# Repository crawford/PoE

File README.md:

# Power over Ethernet #

## Development ###

This project makes use of git commit hooks. Configure git to use them by running the following from the root of the repository:

    git config --local core.hooksPath .githooks/

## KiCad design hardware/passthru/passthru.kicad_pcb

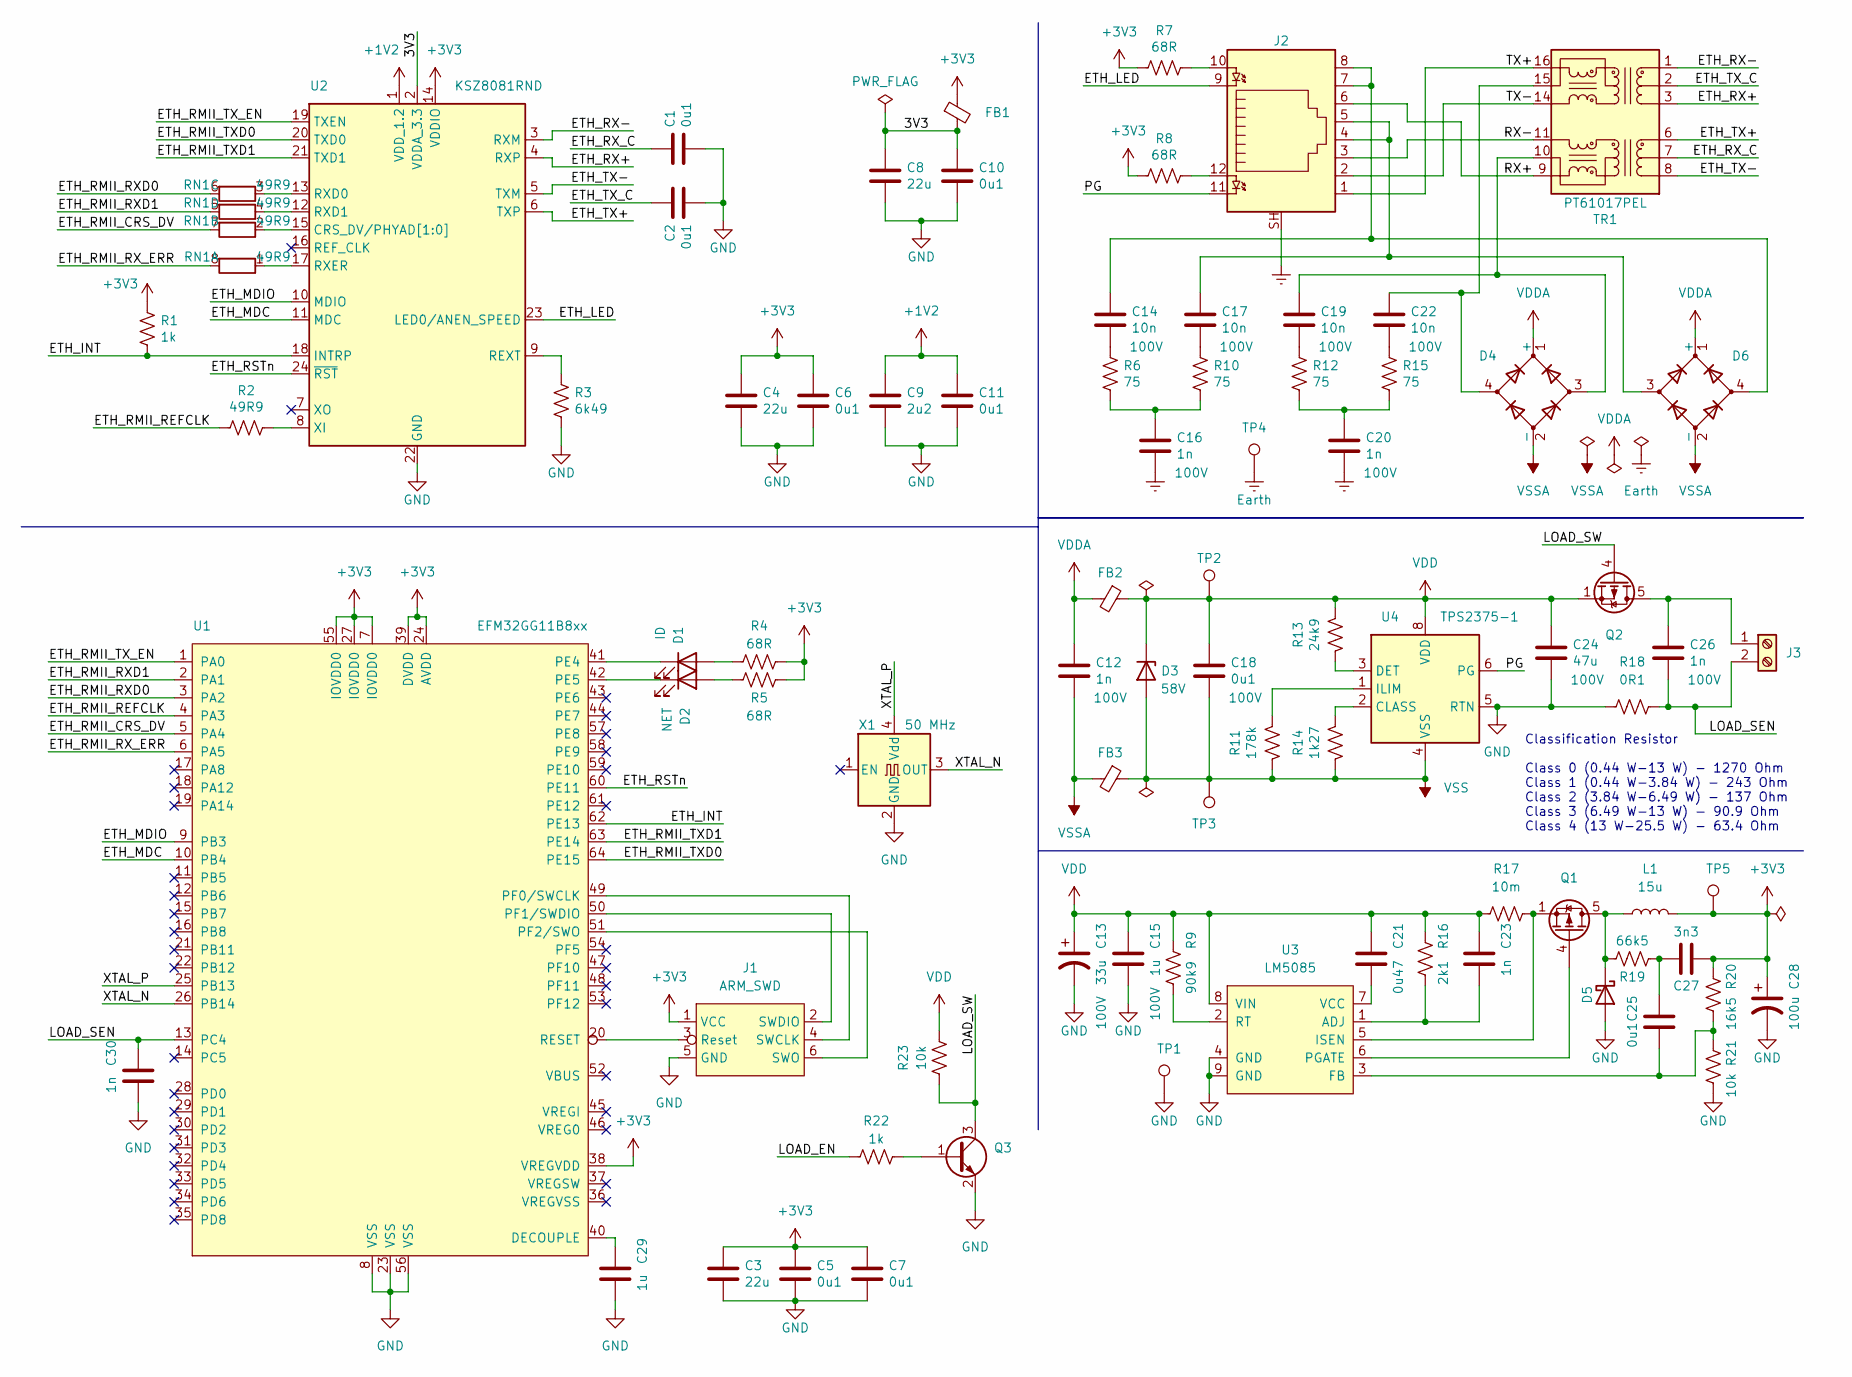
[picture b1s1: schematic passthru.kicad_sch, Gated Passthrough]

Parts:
C1, C2, C5, C6, C7, C10, C11, C25: 0u1; C_0603_1608Metric_Pad1.08x0.95mm_HandSolder
C3, C4, C8: 22u; C_0603_1608Metric_Pad1.08x0.95mm_HandSolder
C9: 2u2; C_0603_1608Metric_Pad1.08x0.95mm_HandSolder
C12, C16, C20, C26: 1n; C_0603_1608Metric_Pad1.08x0.95mm_HandSolder; Voltage 100V
C13: 33u; CP_Elec_10x10; Voltage 100V
C14, C17, C19, C22: 10n; C_0603_1608Metric_Pad1.08x0.95mm_HandSolder; Voltage 100V
C15: 1u; C_0603_1608Metric_Pad1.08x0.95mm_HandSolder; Voltage 100V
C18: 0u1; C_0603_1608Metric_Pad1.08x0.95mm_HandSolder; Voltage 100V
C21: 0u47; C_0603_1608Metric_Pad1.08x0.95mm_HandSolder
C23, C30: 1n; C_0603_1608Metric_Pad1.08x0.95mm_HandSolder
C24: 47u; CP_Elec_10x12.5; Voltage 100V
C27: 3n3; C_0603_1608Metric_Pad1.08x0.95mm_HandSolder
C28: 100u; CP_Elec_6.3x5.8
C29: 1u; C_0603_1608Metric_Pad1.08x0.95mm_HandSolder
D1: ID; LED_D4.0mm
D2: NET; LED_D4.0mm
D3: D_Zener; D_SMA; Voltage 58V
D4, D6: D_Bridge_+-AA; Diode_Bridge_Diotec_ABS
D5: D_Schottky; D_SOD-323F
FB1, FB2, FB3: Ferrite_Bead_Small; L_0603_1608Metric_Pad1.05x0.95mm_HandSolder
J1: ARM_SWD; Tag-Connect_TC2030-IDC-NL_2x03_P1.27mm_Vertical
J2: RJ45_LED_Shielded; RJHSE-338X
J3: Screw_Terminal_01x02; Phoenix_1935161
L1: 15u; L_1210_3225Metric_Pad1.42x2.65mm_HandSolder
Q1, Q2: Q_PMOS_DGS; PowerPAK_SO-8_Single
Q3: Q_NPN_BEC; SOT-23
R1, R22: 1k; R_0603_1608Metric_Pad0.98x0.95mm_HandSolder
R2: 49R9; R_0603_1608Metric_Pad0.98x0.95mm_HandSolder
R3: 6k49; R_0603_1608Metric_Pad0.98x0.95mm_HandSolder
R4, R5, R7, R8: 68R; R_0603_1608Metric_Pad0.98x0.95mm_HandSolder
R6, R10, R12, R15: 75; R_0603_1608Metric_Pad0.98x0.95mm_HandSolder
R9: 90k9; R_0603_1608Metric_Pad0.98x0.95mm_HandSolder
R11: 178k; R_0603_1608Metric_Pad0.98x0.95mm_HandSolder
R13: 24k9; R_0603_1608Metric_Pad0.98x0.95mm_HandSolder
R14: 1k27; R_0603_1608Metric_Pad0.98x0.95mm_HandSolder
R16: 2k1; R_0603_1608Metric_Pad0.98x0.95mm_HandSolder
R17: 10m; R_0603_1608Metric_Pad0.98x0.95mm_HandSolder
R18: 0R1; R_0805_2012Metric_Pad1.20x1.40mm_HandSolder
R19: 66k5; R_0603_1608Metric_Pad0.98x0.95mm_HandSolder
R20: 16k5; R_0603_1608Metric_Pad0.98x0.95mm_HandSolder
R21, R23: 10k; R_0603_1608Metric_Pad0.98x0.95mm_HandSolder
RN1: 49R9; R_Cat16-4
TP1: GND; TestPoint_Loop_D1.80mm_Drill1.0mm_Beaded
TP2: VDD; TestPoint_Loop_D1.80mm_Drill1.0mm_Beaded
TP3: VSS; TestPoint_Loop_D1.80mm_Drill1.0mm_Beaded
TP4: EARTH; TestPoint_Loop_D1.80mm_Drill1.0mm_Beaded
TP5: 3V3; TestPoint_Loop_D1.80mm_Drill1.0mm_Beaded
TR1: PT61017PEL
U1: EFM32GG11B8xx; QFP-64
U2: KSZ8081RND; QFN-24
U3: LM5085; WSON-8-1EP_3x3mm_P0.5mm_EP1.6x2.0mm
U4: TPS2375-1; TSSOP-8_4.4x3mm_P0.65mm
X1: 50 MHz; Oscillator_SMD_Abracon_ASE-4Pin_3.2x2.5mm

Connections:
+1V2: C9.1, C11.1, U2.1 (VDD_1.2)
+3V3: C3.1, C4.1, C5.1, C6.1, C7.1, C27.1, C28.1, FB1.1, J1.1 (VCC), L1.2, R1.1, R4.2, R5.2, R7.2, R8.2, R20.1, TP5.1, U1.7 (IOVDD0), U1.24 (AVDD), U1.27 (IOVDD0), U1.38 (VREGVDD), U1.39 (DVDD), U1.55 (IOVDD0), U2.14 (VDDIO)
/3V3: C8.1, C10.1, FB1.2, U2.2 (VDDA_3.3)
/ETH_INT: R1.2, U1.62 (PE13), U2.18 (INTRP)
/ETH_LED: J2.9, U2.23 (LED0/ANEN_SPEED)
/ETH_MDC: U1.10 (PB4), U2.11 (MDC)
/ETH_MDIO: U1.9 (PB3), U2.10 (MDIO)
/ETH_RMII_CRS_DV: RN1.7 (R2.2), U1.5 (PA4)
/ETH_RMII_REFCLK: R2.2, U1.4 (PA3)
/ETH_RMII_RXD0: RN1.6 (R3.2), U1.3 (PA2)
/ETH_RMII_RXD1: RN1.5 (R4.2), U1.2 (PA1)
/ETH_RMII_RX_ERR: RN1.8 (R1.2), U1.6 (PA5)
/ETH_RMII_TXD0: U1.64 (PE15), U2.20 (TXD0)
/ETH_RMII_TXD1: U1.63 (PE14), U2.21 (TXD1)
/ETH_RMII_TX_EN: U1.1 (PA0), U2.19 (TXEN)
/ETH_RSTn: U1.60 (PE11), U2.24 (~RST)
/ETH_RX+: TR1.3 (TD-), U2.4 (RXP)
/ETH_RX-: TR1.1 (TD+), U2.3 (RXM)
/ETH_RX_C: C1.1, TR1.7 (C_RD)
/ETH_TX+: TR1.6 (RD+), U2.6 (TXP)
/ETH_TX-: TR1.8 (RD-), U2.5 (TXM)
/ETH_TX_C: C2.1, TR1.2 (C_TD)
/LOAD_EN: R22.1
/LOAD_SEN: C26.2, C30.1, J3.2, R18.2, U1.13 (PC4)
/LOAD_SW: Q2.4 (G), Q3.3 (C), R23.1
/PG: J2.11, U4.6 (PG)
/RX+: J2.6, TR1.9 (RX-)
/RX-: J2.3, TR1.11 (RX+)
/TX+: J2.1, TR1.16 (TX+)
/TX-: J2.2, TR1.14 (TX-)
/XTAL_N: U1.26 (PB14), X1.3 (OUT)
/XTAL_P: U1.25 (PB13), X1.4 (Vdd)
Earth: C16.2, C20.2, J2.SH, TP4.1
GND: C1.2, C2.2, C3.2, C4.2, C5.2, C6.2, C7.2, C8.2, C9.2, C10.2, C11.2, C13.2, C15.2, C24.2, C28.2, C29.2, C30.2, D5.2 (A), J1.5 (GND), Q3.2 (E), R3.2, R18.1, R21.2, TP1.1, U1.8 (VSS), U1.23 (VSS), U1.56 (VSS), U2.22 (GND), U2.25 (GND), U3.4 (GND), U3.9 (GND), U4.5 (RTN), X1.2 (GND)
unnamed: C14.1, D6.4, J2.7, J2.8
unnamed: C14.2, R6.1
unnamed: C16.1, R6.2, R10.2
unnamed: C17.1, D6.3, J2.4, J2.5
unnamed: C17.2, R10.1
unnamed: C19.1, D4.3, TR1.10 (C_RX)
unnamed: C19.2, R12.1
unnamed: C20.1, R12.2, R15.2
unnamed: C21.2, U3.7 (VCC)
unnamed: C22.1, D4.4, TR1.15 (C_TX)
unnamed: C22.2, R15.1
unnamed: C23.1, R16.1, U3.1 (ADJ)
unnamed: C25.1, R20.2, R21.1, U3.3 (FB)
unnamed: C25.2, C27.2, R19.1
unnamed: C26.1, J3.1, Q2.5 (D)
unnamed: C29.1, U1.40 (DECOUPLE)
unnamed: D1.1 (K), U1.41 (PE4)
unnamed: D1.2 (A), R4.1
unnamed: D2.1 (K), U1.42 (PE5)
unnamed: D2.2 (A), R5.1
unnamed: D5.1 (K), L1.1, Q1.5 (D), R19.2
unnamed: J1.2 (SWDIO), U1.50 (PF1/SWDIO)
unnamed: J1.3 (Reset), U1.20 (RESET)
unnamed: J1.4 (SWCLK), U1.49 (PF0/SWCLK)
unnamed: J1.6 (SWO), U1.51 (PF2/SWO)
unnamed: J2.10, R7.1
unnamed: J2.12, R8.1
unnamed: Q1.1 (S), Q1.2 (S), Q1.3 (S), R17.2, U3.5 (ISEN)
unnamed: Q1.4 (G), U3.6 (PGATE)
unnamed: Q3.1 (B), R22.2
unnamed: R2.1, U2.8 (XI)
unnamed: R3.1, U2.9 (REXT)
unnamed: R9.1, U3.2 (RT)
unnamed: R11.2, U4.1 (ILIM)
unnamed: R13.1, U4.3 (DET)
unnamed: R14.2, U4.2 (CLASS)
unnamed: RN1.1 (R1.1), U2.17 (RXER)
unnamed: RN1.2 (R2.1), U2.15 (CRS_DV/PHYAD[1:0])
unnamed: RN1.3 (R3.1), U2.13 (RXD0)
unnamed: RN1.4 (R4.1), U2.12 (RXD1)
VDD: C13.1, C15.1, C18.1, C21.1, C23.2, C24.1, D3.1 (K), FB2.1, Q2.1 (S), Q2.2 (S), Q2.3 (S), R9.2, R13.2, R16.2, R17.1, R23.2, TP2.1, U3.8 (VIN), U4.8 (VDD)
VDDA: C12.1, D4.1 (+), D6.1 (+), FB2.2
VSS: C18.2, D3.2 (A), FB3.1, R11.1, R14.1, TP3.1, U4.4 (VSS)
VSSA: C12.2, D4.2 (-), D6.2 (-), FB3.2

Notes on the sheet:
Classification Resistor Class 0 (0.44 W-13 W) - 1270 Ohm Class 1 (0.44 W-3.84 W) - 243 Ohm Class 2 (3.84 W-6.49 W) - 137 Ohm Class 3 (6.49 W-13 W) - 90.9 Ohm Class 4 (13 W-25.5 W) - 63.4 Ohm

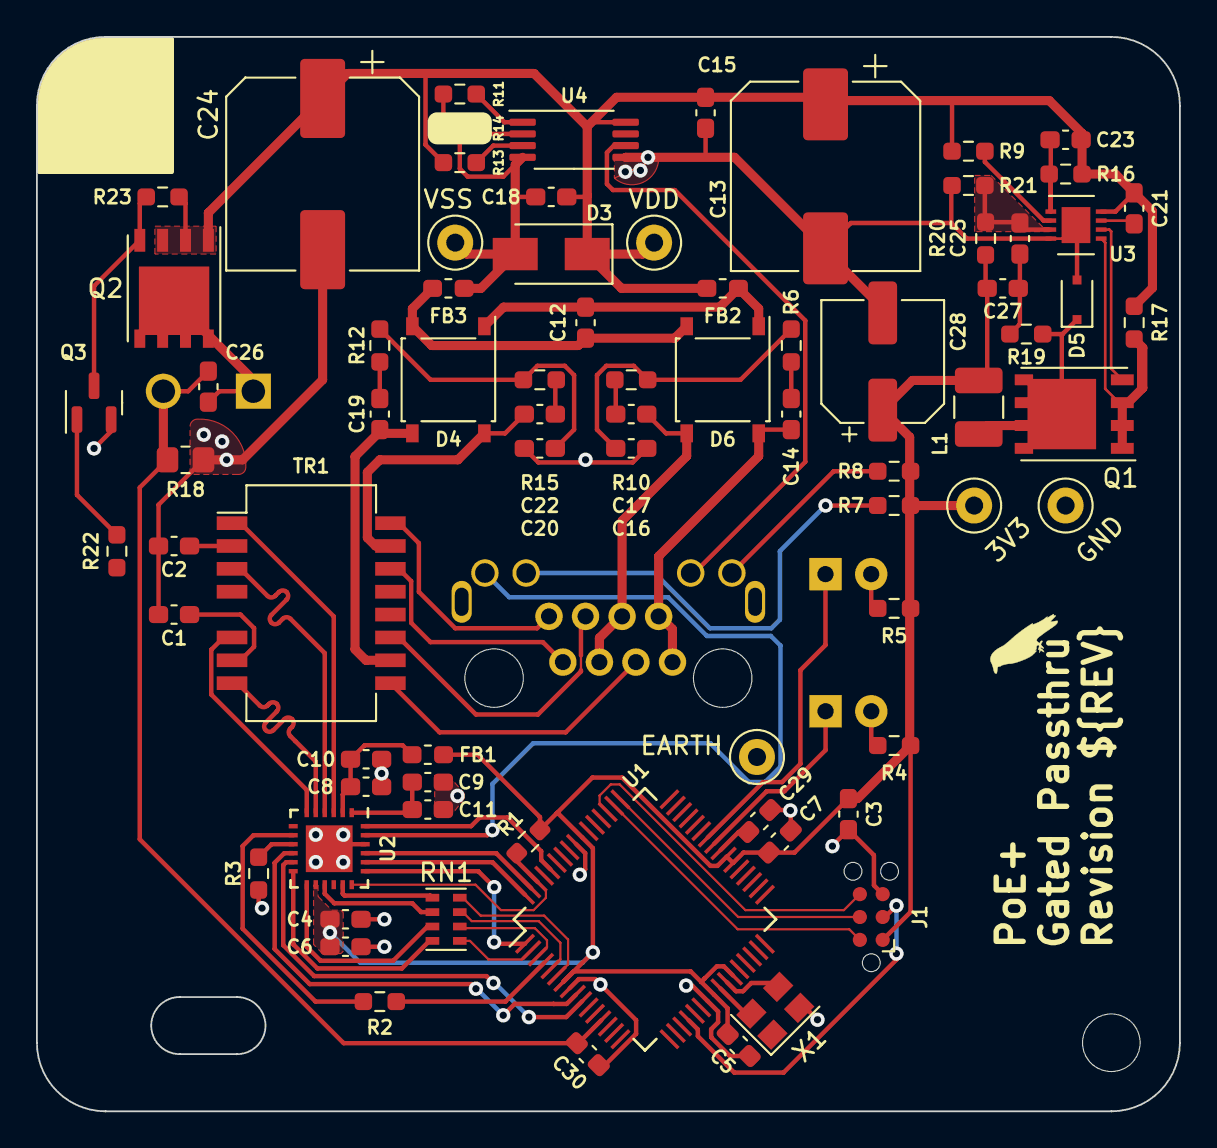
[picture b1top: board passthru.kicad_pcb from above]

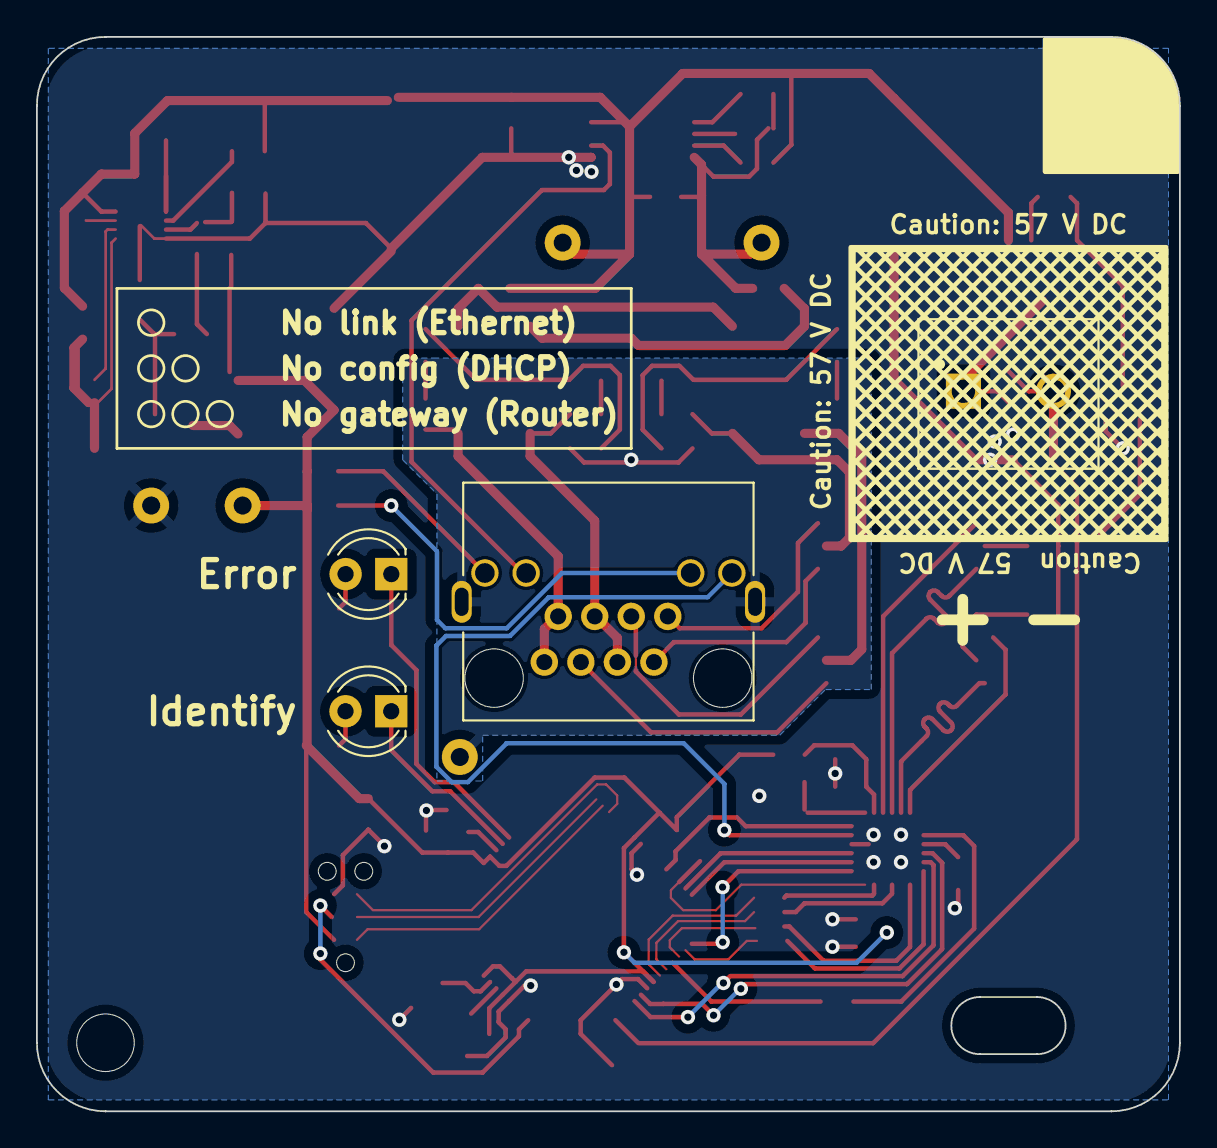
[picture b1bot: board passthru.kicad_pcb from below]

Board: 2 copper layers, 63.5 x 59.7 mm, 81 parts (4 on the bottom side), 77 nets.

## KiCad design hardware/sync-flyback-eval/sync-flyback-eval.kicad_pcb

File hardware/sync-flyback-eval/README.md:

# Synchronous Flyback Converter Evaluation #

## Test Plan ##

### Core Converter ###

Populate:
  1. FB1-FB2
  2. R2-R3, R5-R14, R19-R21, R23-R25
  3. RV1-RV4
  4. L1-L2
  5. C1-C12, C15-C17, C22, C24, C26-C28
  6. D1-D2, D6
  7. Q1-Q3A
  8. U2
  9. T1-T2

Tune:
  1. Set RV1 to 22.1 kΩ.
  2. Set RV2 to 69.8 kΩ.
  3. Set RV3 to 69.8 kΩ.
  4. Set RV4 to 115 kΩ.

Test:
  1. Insufficient supply
    a. Apply 5-volt supply across VDDA (TP10) and VSSA (TP11).
    b. Measure voltage across R7 and verify that it is 0 V.

  2. 24-volt supply
    a. Apply 470-ohm resistance across +12V (TP8) and GNDD (TP13).
    b. Apply 24-volt supply across VDDA and VSSA.
    c. Measure voltage across R8 and verify that it is 255 μV.
    d. Measure voltage across R7 and verify that it is ~181 μV.

  3. 48-volt supply
    a. Connect 470-ohm resistance across +12V (TP8) and GNDD (TP13).
    b. Connect 24-volt supply across VDDA and VSSA.
    c. Measure voltage across R8 and verify that it is 255 μV.
    d. Measure voltage across R7 and verify that it is ~128 μV.

### Power over Ethernet ###

Populate:
  1. J1
  2. TR1
  3. C13-C14, C18-C21, C25
  4. R1, R15-R18
  5. D3-D5

Test:
  1. Passive PoE
    a. Connect to passive (24-volt) PoE PS.
    b. Measure voltage across VDDA and VSSA and verify that it is ~24 V.
    c. Verify that the yellow LED turns on.

  2. PoE+
    a. Connect 470-ohm resistance across +12V and GNDD.
    b. Connect to PoE+ PS.
    c. Measure voltage across VDDA and VSSA and verify that is is 37-57 V.
    d. Verify that the yellow LED turns on.

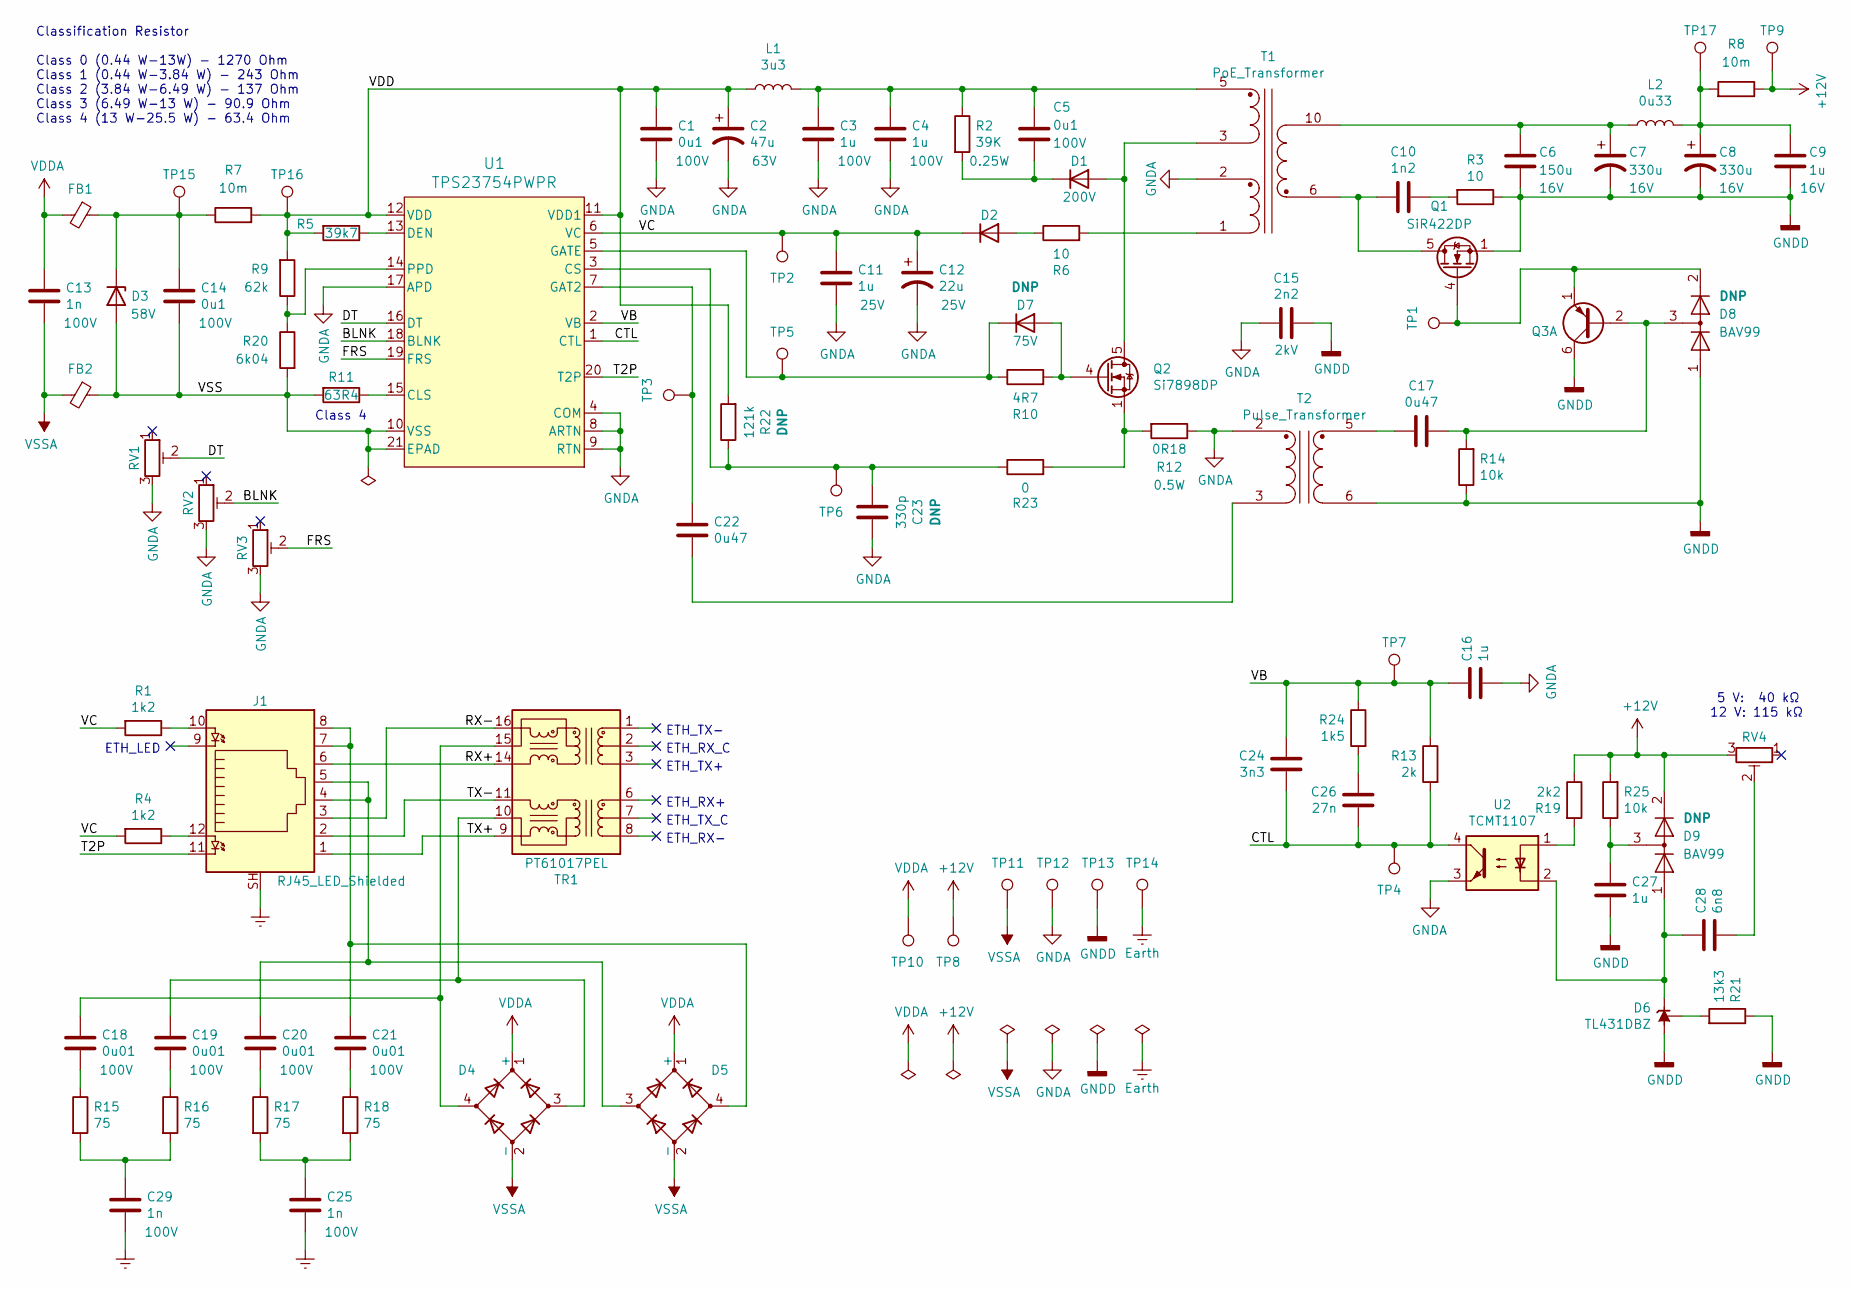
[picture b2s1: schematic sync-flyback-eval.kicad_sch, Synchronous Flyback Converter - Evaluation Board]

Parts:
C1, C5, C14: 0u1; C_0402_1005Metric; Voltage 100V
C2: 47u; C_Elec_8x10.2; Voltage 63V
C3, C4: 1u; C_0805_2012Metric; Voltage 100V
C6: 150u; C_Elec_6.3x7.7; Voltage 16V
C7, C8: 330u; C_Elec_8x10.2; Voltage 16V
C9: 1u; C_0402_1005Metric; Voltage 16V
C10: 1n2; C_0402_1005Metric
C11: 1u; C_0402_1005Metric; Voltage 25V
C12: 22u; C_Elec_5x5.4; Voltage 25V
C13, C25, C29: 1n; C_0402_1005Metric; Voltage 100V
C15: 2n2; C_Disc_D10.0mm_W2.5mm_P5.00mm; Voltage 2kV
C16, C27: 1u; C_0402_1005Metric
C17, C22: 0u47; C_0402_1005Metric
C18, C19, C20, C21: 0u01; C_0402_1005Metric; Voltage 100V
C23: 330p; C_0402_1005Metric
C24: 3n3; C_0402_1005Metric
C26: 27n; C_0402_1005Metric
C28: 6n8; C_0402_1005Metric
D1: D; D_SMB; Voltage 200V
D2: D; D_SOD-323
D3: D_Zener; D_SMA; Voltage 58V
D4, D5: D_Bridge_+-AA; Diode_Bridge_Diotec_ABS
D6: TL431DBZ; SOT-23
D7: D; D_SOD-323; Voltage 75V
D8, D9: BAV99; SOT-23
FB1, FB2: Ferrite_Bead_Small; R_1206_3216Metric
J1: RJ45_LED_Shielded; RJHSE-538X
L1: 3u3; L_Abracon_ASPI-0630LR
L2: 0u33; L_Abracon_ASPI-0630LR
Q1: SiR422DP; PowerPAK_SO-8_Single
Q2: Si7898DP; PowerPAK_SO-8_Single
Q3: MMDT3906; SOT-363_SC-70-6
R1, R4: 1k2; R_0402_1005Metric
R2: 39K; R_0805_2012Metric
R3, R6: 10; R_0805_2012Metric
R5: 39k7; R_0402_1005Metric
R7, R8: 10m; R_0402_1005Metric
R9: 62k; R_0402_1005Metric
R10: 4R7; R_0402_1005Metric
R11: 63R4; R_0402_1005Metric
R12: 0R18; R_0805_2012Metric
R13: 2k; R_0402_1005Metric
R14, R25: 10k; R_0402_1005Metric
R15, R16, R17, R18: 75; R_0402_1005Metric
R19: 2k2; R_0402_1005Metric
R20: 6k04; R_0402_1005Metric
R21: 13k3; R_0402_1005Metric
R22: 121k; R_0402_1005Metric
R23: 0; R_0402_1005Metric
R24: 1k5; R_0402_1005Metric
RV1, RV2, RV3, RV4: 0-200k; TRIM_3306F-1-204
T1: PoE_Transformer; WE-PoE+
T2: Pulse_Transformer; WE-GDTI
TP1: TestPoint; TestPoint_Pad_1.5x1.5mm
TP2: VC; TestPoint_Loop_D1.80mm_Drill1.0mm_Beaded
TP3: GAT2; TestPoint_Pad_1.5x1.5mm
TP4: CTL; TestPoint_Pad_1.5x1.5mm
TP5: GAT; TestPoint_Pad_1.5x1.5mm
TP6: CS; TestPoint_Pad_1.5x1.5mm
TP7, TP9, TP15, TP16, TP17: VB; TestPoint_Loop_D1.80mm_Drill1.0mm_Beaded
TP8: 12V; TestPoint_Loop_D1.80mm_Drill1.0mm_Beaded
TP10: VDDA1; TestPoint_Loop_D1.80mm_Drill1.0mm_Beaded
TP11: VSSA1; TestPoint_Loop_D1.80mm_Drill1.0mm_Beaded
TP12, TP13: GND; TestPoint_Loop_D1.80mm_Drill1.0mm_Beaded
TP14: EARTH; TestPoint_Loop_D1.80mm_Drill1.0mm_Beaded
TR1: PT61017PEL
U1: TPS23754PWPR; TSSOP-20
U2: TCMT1107; SOP-4_4.4x2.6mm_P1.27mm

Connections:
+12V: D9.2 (A), R8.1, R19.1, R25.2, RV4.3, TP8.1, TP9.1
/BLNK: RV2.2, U1.18 (BLNK)
/CTL: C24.2, C26.2, R13.2, TP4.1, U1.1 (CTL), U2.4
/DT: RV1.2, U1.16 (DT)
/FRS: RV3.2, U1.19 (FRS)
/RX+: J1.6, TR1.14 (TX-)
/RX-: J1.3, TR1.16 (TX+)
/T2P: J1.11, U1.20 (T2P)
/TX+: J1.1, TR1.9 (RX-)
/TX-: J1.2, TR1.11 (RX+)
/VB: C16.1, C24.1, R13.1, R24.1, TP7.1, U1.2 (VB)
/VC: C11.1, C12.1, D2.1 (K), R1.2, R4.2, TP2.1, U1.6 (VC)
/VDD: C1.1, C2.1, L1.1, R5.2, R7.2, R9.2, R22.2, TP16.1, U1.11 (VDD1), U1.12 (VDD)
/VSS: C14.2, D3.2 (A), FB2.1, R11.2, R20.2, U1.10 (VSS), U1.21 (EPAD)
Earth: C25.2, C29.2, J1.SH, TP14.1
GNDA: C1.2, C2.2, C3.2, C4.2, C11.2, C12.2, C15.2, C16.2, C23.1, R12.1, RV1.3, RV2.3, RV3.3, T1.2 (SC), T2.2 (AA), TP12.1, U1.4 (COM), U1.8 (ARTN), U1.9 (RTN), U1.17 (APD), U2.3
GNDD: C6.2, C7.2, C8.2, C9.2, C15.1, C27.2, D6.3 (A), D8.1 (K), Q1.1 (S), Q1.2 (S), Q1.3 (S), Q3.6 (C1), R3.1, R14.1, R21.1, T2.6 (SA), TP13.1
unnamed: C3.1, C4.1, C5.1, L1.2, R2.1, T1.5 (SA)
unnamed: C5.2, D1.1 (K), R2.2
unnamed: C6.1, C7.1, L2.1, T1.10 (AA)
unnamed: C8.1, C9.1, L2.2, R8.2, TP17.1
unnamed: C10.1, R3.2
unnamed: C10.2, Q1.5 (D), T1.6 (AB)
unnamed: C14.1, D3.1 (K), FB1.1, R7.1, TP15.1
unnamed: C17.1, D8.3 (K), Q3.2 (B1), R14.2
unnamed: C17.2, T2.5 (SB)
unnamed: C18.1, D4.4, TR1.15 (C_TX)
unnamed: C18.2, R15.1
unnamed: C19.1, D4.3, TR1.10 (C_RX)
unnamed: C19.2, R16.1
unnamed: C20.1, D5.3, J1.4, J1.5
unnamed: C20.2, R17.1
unnamed: C21.1, D5.4, J1.7, J1.8
unnamed: C21.2, R18.1
unnamed: C22.1, T2.3 (AB)
unnamed: C22.2, TP3.1, U1.7 (GAT2)
unnamed: C23.2, R22.1, R23.1, TP6.1, U1.3 (CS)
unnamed: C25.1, R17.2, R18.2
unnamed: C26.1, R24.2
unnamed: C27.1, D9.3 (K), R25.1
unnamed: C28.1, D6.1 (K), D9.1 (K), U2.2
unnamed: C28.2, RV4.2
unnamed: C29.1, R15.2, R16.2
unnamed: D1.2 (A), Q2.5 (D), T1.3 (SB)
unnamed: D2.2 (A), R6.1
unnamed: D6.2 (REF), R21.2
unnamed: D7.1 (K), R10.1, TP5.1, U1.5 (GATE)
unnamed: D7.2 (A), Q2.4 (G), R10.2
unnamed: D8.2 (A), Q1.4 (G), Q3.1 (E1), TP1.1
unnamed: J1.10, R1.1
unnamed: J1.12, R4.1
unnamed: Q2.1 (S), Q2.2 (S), Q2.3 (S), R12.2, R23.2
unnamed: R5.1, U1.13 (DEN)
unnamed: R6.2, T1.1 (SD)
unnamed: R11.1, U1.15 (CLS)
unnamed: R19.2, U2.1
unnamed: R9.1, R20.1, U1.14 (PPD)
VDDA: C13.1, D4.1 (+), D5.1 (+), FB1.2, TP10.1
VSSA: C13.2, D4.2 (-), D5.2 (-), FB2.2, TP11.1

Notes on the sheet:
5 V: 40 kΩ 12 V: 115 kΩ
ETH_RX_C
ETH_LED
ETH_TX-
ETH_TX+
Classification Resistor Class 0 (0.44 W-13W) - 1270 Ohm Class 1 (0.44 W-3.84 W) - 243 Ohm Class 2 (3.84 W-6.49 W) - 137 Ohm Class 3 (6.49 W-13 W) - 90.9 Ohm Class 4 (13 W-25.5 W) - 63.4 Ohm
ETH_RX-
ETH_RX+
ETH_TX_C
Class 4

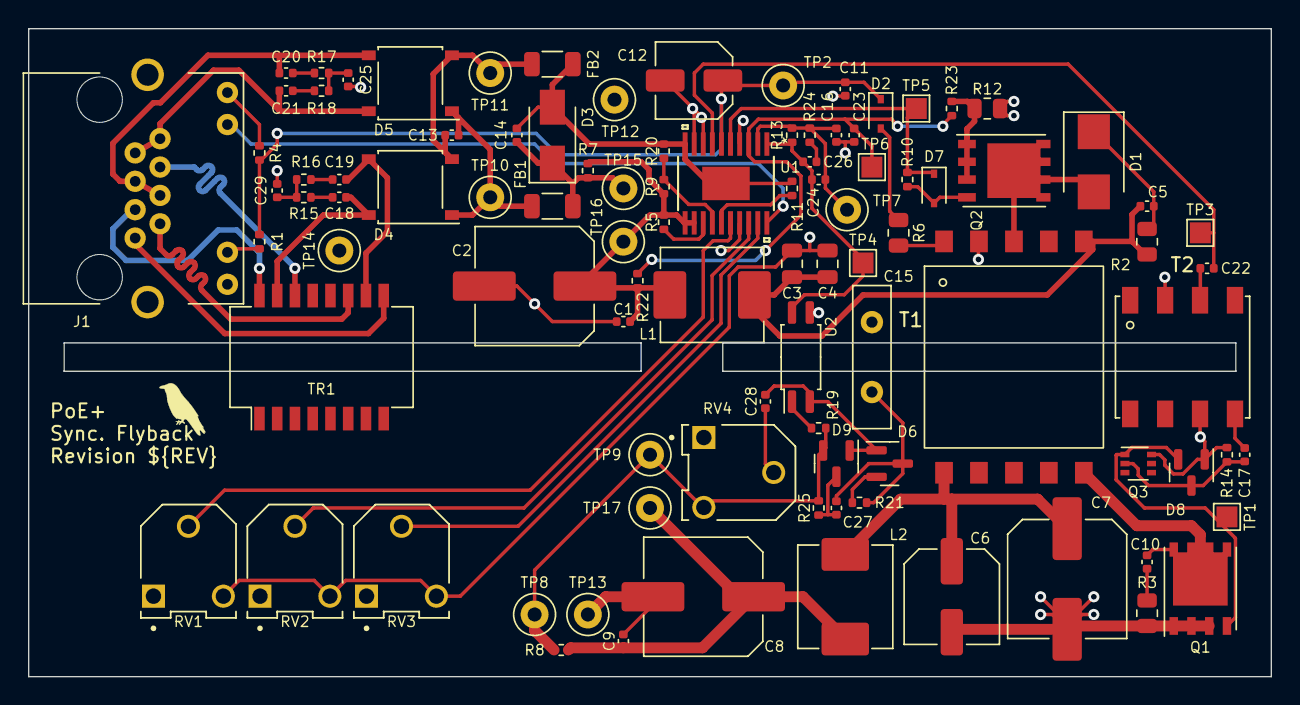
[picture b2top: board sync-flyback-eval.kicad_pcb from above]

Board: 2 copper layers, 88.9 x 46.4 mm, 97 parts (0 on the bottom side), 59 nets.

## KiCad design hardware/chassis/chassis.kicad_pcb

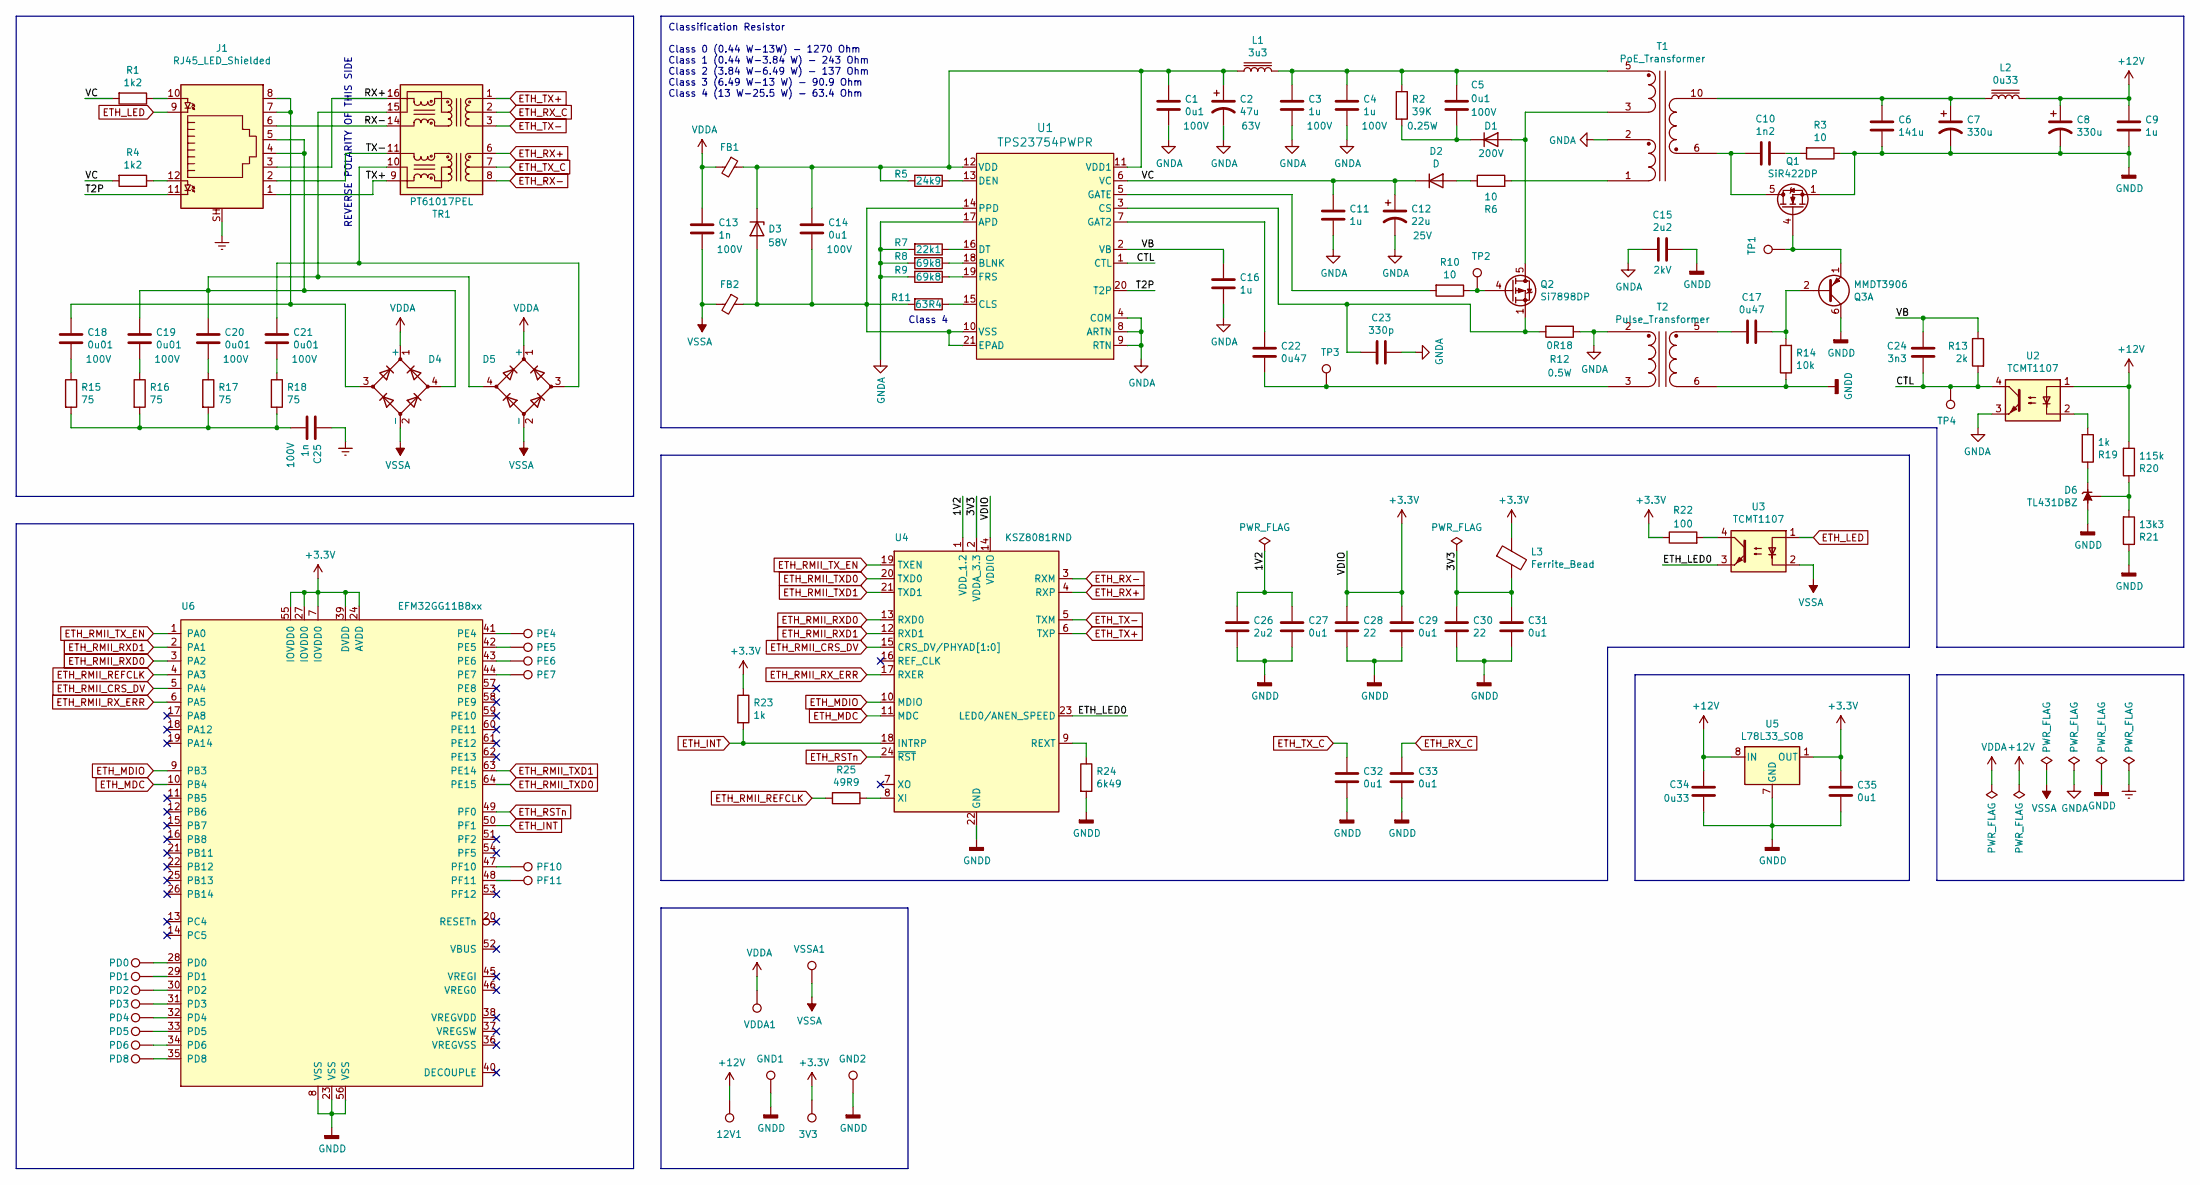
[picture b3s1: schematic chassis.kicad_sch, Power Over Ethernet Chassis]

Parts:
3V3: TestPoint; TestPoint_Pad_1.5x1.5mm
12V1: TestPoint; TestPoint_Loop_D1.80mm_Drill1.0mm_Beaded
C1, C5, C14: 0u1; C_0402_1005Metric; Voltage 100V
C2: 47u; C_0402_1005Metric; Voltage 63V
C3, C4: 1u; C_0402_1005Metric; Voltage 100V
C6: 141u; C_0402_1005Metric
C7, C8: 330u; C_0402_1005Metric
C9, C11, C16: 1u; C_0402_1005Metric
C10: 1n2; C_0402_1005Metric
C12: 22u; C_0402_1005Metric; Voltage 25V
C13, C25: 1n; C_0402_1005Metric; Voltage 100V
C15: 2u2; C_0402_1005Metric; Voltage 2kV
C17, C22: 0u47; C_0402_1005Metric
C18, C19, C20, C21: 0u01; C_0402_1005Metric; Voltage 100V
C23: 330p; C_0402_1005Metric
C24: 3n3; C_0402_1005Metric
C26: 2u2; C_0402_1005Metric
C27, C29, C31, C32, C33, C35: 0u1; C_0402_1005Metric
C28, C30: 22; C_0402_1005Metric
C34: 0u33; C_0402_1005Metric
D1: D; D_0402_1005Metric; Voltage 200V
D2: D; D_0402_1005Metric
D3: D_Zener; D_0402_1005Metric; Voltage 58V
D4, D5: D_Bridge_+-AA; Diode_Bridge_Diotec_ABS
D6: TL431DBZ; SOT-23
FB1, FB2: Ferrite_Bead_Small; R_1206_3216Metric
GND1: TestPoint; TestPoint_Loop_D1.80mm_Drill1.0mm_Beaded
GND2: TestPoint; TestPoint_Pad_1.5x1.5mm
J1: RJ45_LED_Shielded; RJHSE-538X
L1: 3u3; L_0402_1005Metric
L2: 0u33; L_0402_1005Metric
L3: Ferrite_Bead; L_0402_1005Metric
PD0, PD1, PD2, PD3, PD4, PD5, PD6, PD8: TestPoint; TestPoint_Pad_1.5x1.5mm
PE4, PE5, PE6, PE7: TestPoint; TestPoint_Pad_1.5x1.5mm
PF10, PF11: TestPoint; TestPoint_Pad_1.5x1.5mm
Q1: SiR422DP; PowerPAK_SO-8_Single
Q2: Si7898DP; PowerPAK_SO-8_Single
Q3: MMDT3906; SOT-363_SC-70-6
R1, R4: 1k2; R_0402_1005Metric
R2: 39K; R_0402_1005Metric
R3, R6, R10: 10; R_0402_1005Metric
R5: 24k9; R_0402_1005Metric
R7: 22k1; R_0402_1005Metric
R8, R9: 69k8; R_0402_1005Metric
R11: 63R4; R_0402_1005Metric
R12: 0R18; R_0402_1005Metric
R13: 2k; R_0402_1005Metric
R14: 10k; R_0402_1005Metric
R15, R16, R17, R18: 75; R_0402_1005Metric
R19, R23: 1k; R_0402_1005Metric
R20: 115k; R_0402_1005Metric
R21: 13k3; R_0402_1005Metric
R22: 100; R_0402_1005Metric
R24: 6k49; R_0402_1005Metric
R25: 49R9; R_0402_1005Metric
T1: PoE_Transformer; POE_EP13
T2: Pulse_Transformer; GDTI_EP7
TP1, TP2, TP3, TP4: TestPoint; TestPoint_Pad_1.5x1.5mm
TR1: PT61017PEL; Transformer_Ethernet_Bourns_PT61017PEL
U1: TPS23754PWPR; TSSOP-20
U2, U3: TCMT1107; SOP-4_4.4x2.6mm_P1.27mm
U4: KSZ8081RND; QFN-24
U5: L78L33_SO8; SOIC-8_3.9x4.9mm_P1.27mm
U6: EFM32GG11B8xx; QFP-64
VDDA1: TestPoint; TestPoint_Pad_1.5x1.5mm
VSSA1: TestPoint; TestPoint_Pad_1.5x1.5mm

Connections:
+3V3: 3V3.1, C28.1, C29.1, C35.1, L3.1, R22.1, R23.1, U4.14 (VDDIO), U5.1 (OUT), U6.7 (IOVDD0), U6.24 (AVDD), U6.27 (IOVDD0), U6.39 (DVDD), U6.55 (IOVDD0)
+12V: 12V1.1, C8.1, C9.1, C34.1, L2.2, R20.2, U2.1, U5.8 (IN)
/1V2: C26.1, C27.1, U4.1 (VDD_1.2)
/3V3: C30.1, C31.1, L3.2, U4.2 (VDDA_3.3)
/CTL: C24.2, R13.2, TP4.1, U1.1 (CTL), U2.4
/ETH_LED0: U3.3, U4.23 (LED0/ANEN_SPEED)
/RX+: J1.3, TR1.16 (TX+)
/RX-: J1.6, TR1.14 (TX-)
/T2P: J1.11, U1.20 (T2P)
/TX+: J1.1, TR1.9 (RX-)
/TX-: J1.2, TR1.11 (RX+)
/VB: C16.1, C24.1, R13.1, U1.2 (VB)
/VC: C11.1, C12.1, D2.1 (K), R1.2, R4.2, U1.6 (VC)
ETH_INT: R23.2, U4.18 (INTRP), U6.50 (PF1)
ETH_LED: J1.9, U3.1
ETH_MDC: U4.11 (MDC), U6.10 (PB4)
ETH_MDIO: U4.10 (MDIO), U6.9 (PB3)
ETH_RMII_CRS_DV: U4.15 (CRS_DV/PHYAD[1:0]), U6.5 (PA4)
ETH_RMII_REFCLK: R25.2, U6.4 (PA3)
ETH_RMII_RXD0: U4.13 (RXD0), U6.3 (PA2)
ETH_RMII_RXD1: U4.12 (RXD1), U6.2 (PA1)
ETH_RMII_RX_ERR: U4.17 (RXER), U6.6 (PA5)
ETH_RMII_TXD0: U4.20 (TXD0), U6.64 (PE15)
ETH_RMII_TXD1: U4.21 (TXD1), U6.63 (PE14)
ETH_RMII_TX_EN: U4.19 (TXEN), U6.1 (PA0)
ETH_RSTn: U4.24 (~RST), U6.49 (PF0)
ETH_RX+: TR1.6 (RD+), U4.4 (RXP)
ETH_RX-: TR1.8 (RD-), U4.3 (RXM)
ETH_RX_C: C33.1, TR1.2 (C_TD)
ETH_TX+: TR1.1 (TD+), U4.6 (TXP)
ETH_TX-: TR1.3 (TD-), U4.5 (TXM)
ETH_TX_C: C32.1, TR1.7 (C_RD)
Earth: C25.1, J1.SH
GNDA: C1.2, C2.2, C3.2, C4.2, C11.2, C12.2, C15.2, C16.2, C23.1, R7.2, R8.2, R9.2, R12.1, T1.2 (SC), T2.2 (AA), U1.4 (COM), U1.8 (ARTN), U1.9 (RTN), U1.17 (APD), U2.3
GNDD: C6.2, C7.2, C8.2, C9.2, C15.1, C26.2, C27.2, C28.2, C29.2, C30.2, C31.2, C32.2, C33.2, C34.2, C35.2, D6.3 (A), GND1.1, GND2.1, Q1.1 (S), Q1.2 (S), Q1.3 (S), Q3.6 (C1), R3.1, R14.1, R21.1, R24.2, T2.6 (SA), U4.22 (GND), U4.25 (GND), U5.2 (GND), U5.3 (GND), U5.6 (GND), U5.7 (GND), U6.8 (VSS), U6.23 (VSS), U6.56 (VSS)
unnamed: C1.1, C2.1, C14.1, D3.1 (K), FB1.1, L1.1, R5.2, U1.11 (VDD1), U1.12 (VDD)
unnamed: C3.1, C4.1, C5.1, L1.2, R2.1, T1.5 (SA)
unnamed: C5.2, D1.1 (K), R2.2
unnamed: C6.1, C7.1, L2.1, T1.10 (AA)
unnamed: C10.1, R3.2
unnamed: C10.2, Q1.5 (D), T1.6 (AB)
unnamed: C14.2, D3.2 (A), FB2.1, R11.2, U1.10 (VSS), U1.14 (PPD), U1.21 (EPAD)
unnamed: C17.1, Q3.2 (B1), R14.2
unnamed: C17.2, T2.5 (SB)
unnamed: C18.1, D4.3, J1.7, J1.8
unnamed: C18.2, R15.1
unnamed: C19.1, C20.1, D4.4, D5.4, J1.4, J1.5, TR1.15 (C_TX)
unnamed: C19.2, R16.1
unnamed: C20.2, R17.1
unnamed: C21.1, D5.3, TR1.10 (C_RX)
unnamed: C21.2, R18.1
unnamed: C22.1, T2.3 (AB), TP3.1
unnamed: C22.2, U1.7 (GAT2)
unnamed: C23.2, Q2.1 (S), Q2.2 (S), Q2.3 (S), R12.2, U1.3 (CS)
unnamed: C25.2, R15.2, R16.2, R17.2, R18.2
unnamed: D1.2 (A), Q2.5 (D), T1.3 (SB)
unnamed: D2.2 (A), R6.1
unnamed: D6.1 (K), R19.1
unnamed: D6.2 (REF), R20.1, R21.2
unnamed: J1.10, R1.1
unnamed: J1.12, R4.1
unnamed: PD0.1, U6.28 (PD0)
unnamed: PD1.1, U6.29 (PD1)
unnamed: PD2.1, U6.30 (PD2)
unnamed: PD3.1, U6.31 (PD3)
unnamed: PD4.1, U6.32 (PD4)
unnamed: PD5.1, U6.33 (PD5)
unnamed: PD6.1, U6.34 (PD6)
unnamed: PD8.1, U6.35 (PD8)
unnamed: PE4.1, U6.41 (PE4)
unnamed: PE5.1, U6.42 (PE5)
unnamed: PE6.1, U6.43 (PE6)
unnamed: PE7.1, U6.44 (PE7)
unnamed: PF10.1, U6.47 (PF10)
unnamed: PF11.1, U6.48 (PF11)
unnamed: Q1.4 (G), Q3.1 (E1), TP1.1
unnamed: Q2.4 (G), R10.1, TP2.1
unnamed: R5.1, U1.13 (DEN)
unnamed: R6.2, T1.1 (SD)
unnamed: R7.1, U1.16 (DT)
unnamed: R8.1, U1.18 (BLNK)
unnamed: R9.1, U1.19 (FRS)
unnamed: R10.2, U1.5 (GATE)
unnamed: R11.1, U1.15 (CLS)
unnamed: R19.2, U2.2
unnamed: R22.2, U3.4
unnamed: R24.1, U4.9 (REXT)
unnamed: R25.1, U4.8 (XI)
VDDA: C13.1, D4.1 (+), D5.1 (+), FB1.2, VDDA1.1
VSSA: C13.2, D4.2 (-), D5.2 (-), FB2.2, U3.2, VSSA1.1

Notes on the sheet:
REVERSE POLARITY OF THIS SIDE
Classification Resistor Class 0 (0.44 W-13W) - 1270 Ohm Class 1 (0.44 W-3.84 W) - 243 Ohm Class 2 (3.84 W-6.49 W) - 137 Ohm Class 3 (6.49 W-13 W) - 90.9 Ohm Class 4 (13 W-25.5 W) - 63.4 Ohm
Class 4

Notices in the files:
firmware/src/efm32gg/mod.rs:
Copyright 2018 Alex Crawford
This program is free software: you can redistribute it and/or modify
it under the terms of the GNU General Public License as published by
the Free Software Foundation, either version 3 of the License, or
any later version.
software/supervisor/src/bin/passthru.rs:
Copyright 2023 Alex Crawford
parts and their libraries:
Copyright 2016 Accelerated Designs. All rights reserved.
